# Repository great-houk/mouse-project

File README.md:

# Custom Mouse V1.0

This project is an all contains every piece you would need to fully order, assemble, and program a completely open source mouse.

This is only the first version of this mouse, and the end goal of this project is no where near complete. However, this first version does 100% work 90% of the time, so the inital goal of making a mouse is complete. In fact, I'm using it to write this readme. Pretty neat.

My immediate goal is to implement the wireless protocol over the SR1020 radio.

Future versions of this project won't use a barebones $15 dollar mouse off of amazon, and will have much higher quality everything, while also hopefully being cheaper. I used a lot of parts on this, like the MAX32625, because they looked cool. The 32625 has a one of a kind PMU, which is something like another set of super low power cores you can manually program through assembly. While this seems awesome at first, and like the perfect tool to reach extra efficient power targets, in the end the sensor draws >20mW anyway, so the difference of ~1-2mW the PMU provides is useless, and so it the extra cost.

# Notes for making your own

This is the mouse I bought and used as a base: [Amazon Link](https://www.amazon.com/gp/product/B07ZHFCM43/ref=ppx_yo_dt_b_search_asin_title?ie=UTF8&th=1)

For obtaining the other parts:
1. Most mouse parts can be desoldered from the mouse itself. I only bought one switch for the dongle off of digikey.
2. All other digital parts except the sensor can be obtained from digikey for reasonable prices, and the objects in the Kicad PCB should have digikey links associated with them already.
3. The mouse sensor is hard to get. If you are a student like me, you might be able to get a free sample from Pixart. If you aren't there are a couple of ebay postings or other second hand sellers which might offer them, but they take a while (>month normally) to ship. Pixart does offer to sell the sensors directly, but there is a minimum order quantity of 25.
4. I used JLCPCB to obtain the PCB. I had them make a stencil as well, in order to greatly simply to soldering process. For anyone in the US, chances are JLC is your best bet, for Europe, I've heard of other cheap PCB manufacturers which might do a better job, as long as the shipping isn't prohibitively expensive.
5. Programming the MCU. I used the [MCU Link](https://www.nxp.com/design/microcontrollers-developer-resources/mcu-link-debug-probe:MCU-LINK) with OpenOCD to program the chip, which had all the features I ended up needing. Maxim offers a custom fork of OpenOCD which comes the neccessary files for uploading to the MAX32625, and I made a simple custom file for the MCU Link, which is inside of the mouse folder. You need to place that file in the OpenOCD board config directory, and most online tutuorials should cover that.

The PCB is specifically designed around fitting in the mouse, and even then there were some mistakes I made. Most notably, the top right post hole was misplaced, so that needs to be cut flush so the PCB can rest flat. The antenna also sticks out the side, so you need to cut some small segments off of the casing in order to have it fit. Finally, the USB-C port is in a slightly lower and different place, so you need to cut the sides of the USB port out to have it fit and be accessible.

It took me many tries to assemble this properly, partially because it was my first time using solder past (which by the way is 100% what you need to use to solder this), and partially because there are no good resources out there for solder of this kind, at least that I could find. If you order the PCB from JLCPCB like I did, make sure to get a stencil, as it will make everything signifigantly easier. There is no need to order a stencil for the back, however, that only requires some careful soldering.

The most important parts when assembling the board are
1. Make sure you spread the paste over the stencil the fewest possible times, preferably in one strong, slow swipe. A good solder paste application makes this process signifigantly easier.
2. Don't leave the paste sitting for too long. You can take your time placing the parts, but after around 2-3 hours the paste will start drying and harden, making parts have a signifigantly higher risk of being blown away when using the heat gun.
3. Make sure to not have the temps too high. I broke my first few boards by creating shorts through burned flux. Don't do what I did.

And that's mostly it. There are other resources out there to help with the specifics, but that covers most of the general details.

# Project Structure

Each folder has it's own README which describes what it does, how it works, and how to use it, except the PCB.

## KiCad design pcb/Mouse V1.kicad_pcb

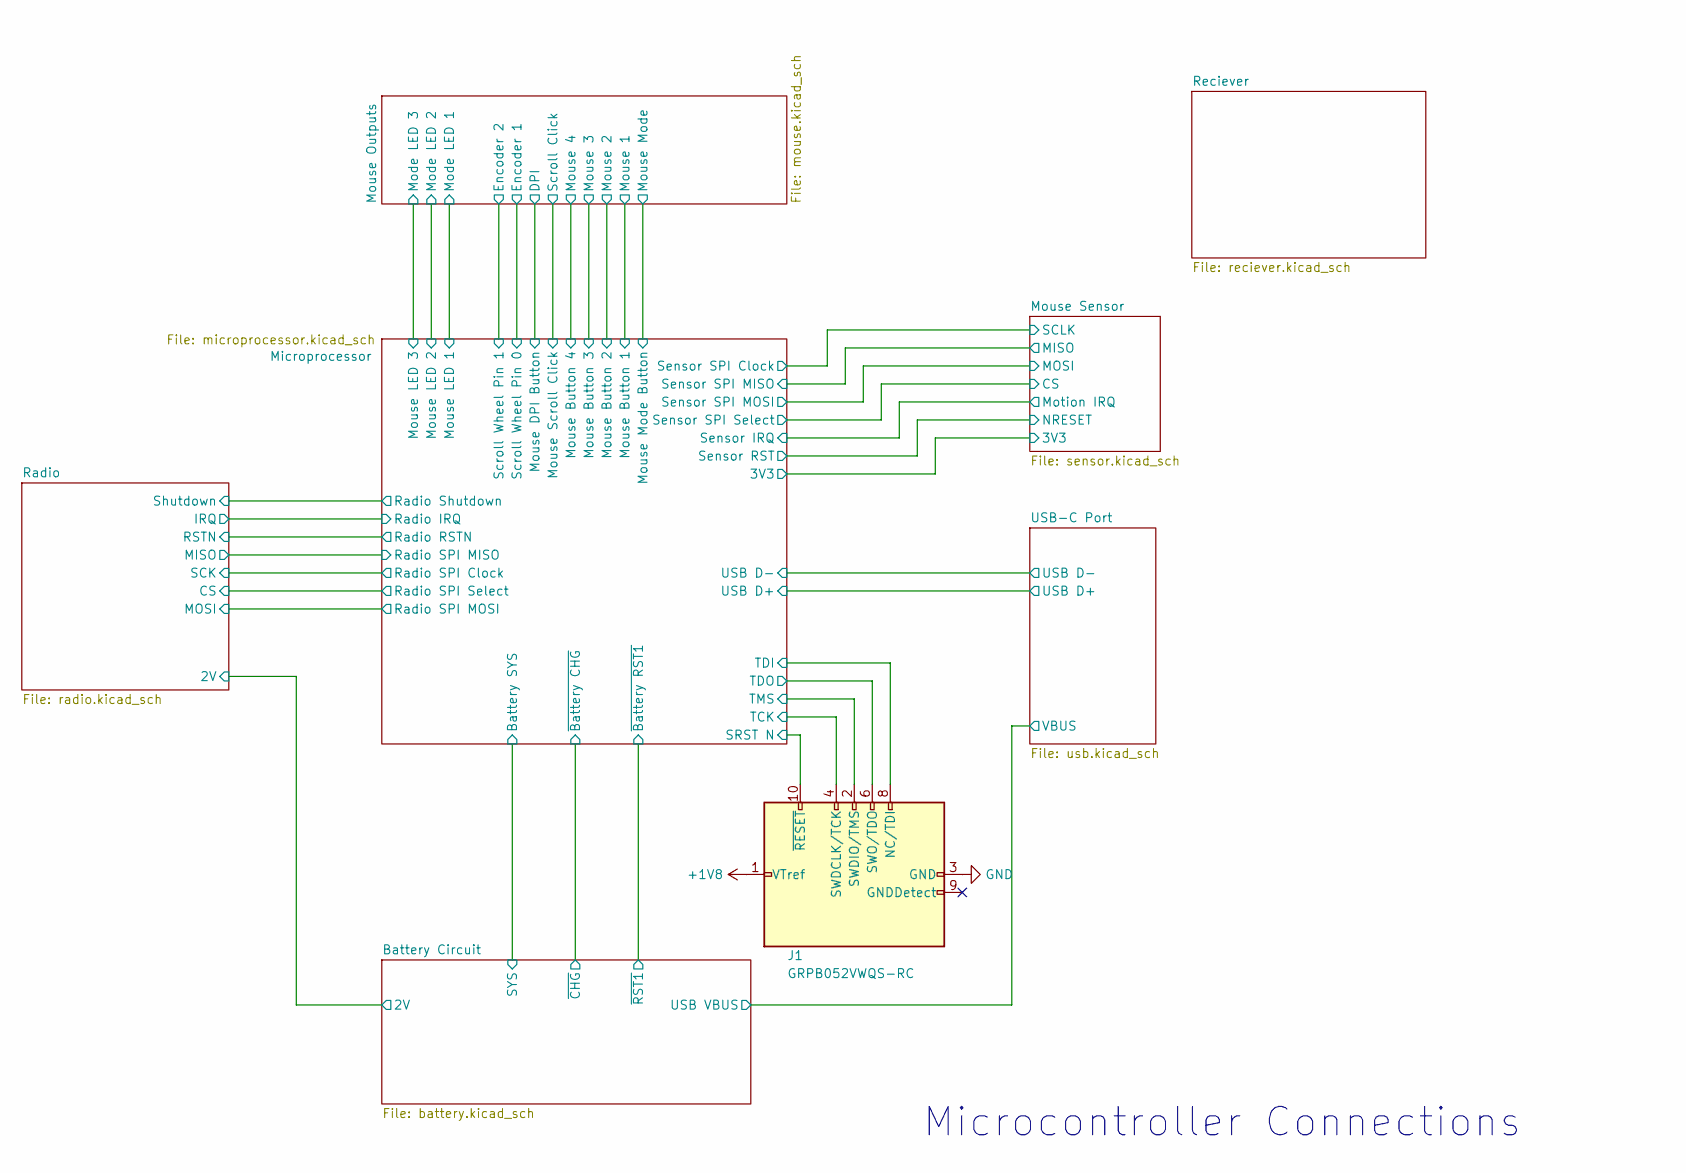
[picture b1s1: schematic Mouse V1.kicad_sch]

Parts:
J1: GRPB052VWQS-RC; PinHeader_2x05_P1.27mm_Vertical_SMD; DIGIKEY GRPB052VWQS-RC

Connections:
+1V8: J1.1 (VTref); also elsewhere on the board
/Microprocessor/SRST N: J1.10 (~RESET); also elsewhere on the board
/Microprocessor/TCK: J1.4 (SWDCLK/TCK); also elsewhere on the board
/Microprocessor/TDI: J1.8 (NC/TDI); also elsewhere on the board
/Microprocessor/TDO: J1.6 (SWO/TDO); also elsewhere on the board
/Microprocessor/TMS: J1.2 (SWDIO/TMS); also elsewhere on the board
GND: J1.3 (GND), J1.5 (GND); also elsewhere on the board

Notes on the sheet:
Microcontroller Connections

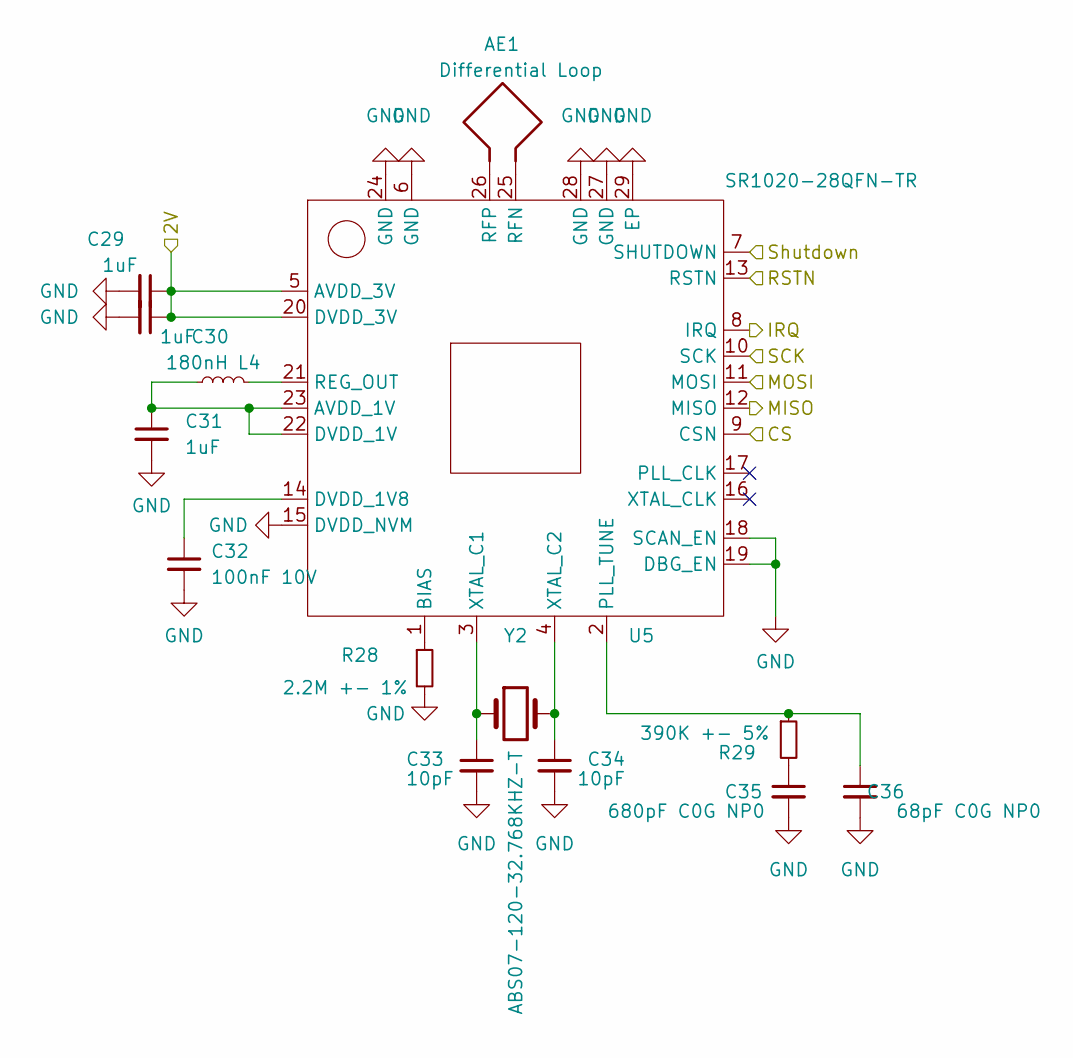
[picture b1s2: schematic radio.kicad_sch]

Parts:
AE1: Differential Loop; SR1020 Antenna Vivaldi
C29, C30, C31: 1uF; C_0603_1608Metric; DIGIKEY CL10A105KA8NNNC
C32: 100nF 10V; C_0603_1608Metric; DIGIKEY CL10B104KB8NNWC
C33, C34: 10pF; C_0603_1608Metric; DIGIKEY 06035A100JAT2A
C35: 680pF C0G NP0; C_0603_1608Metric; DIGIKEY 0603N681J500CT
C36: 68pF C0G NP0; C_0603_1608Metric; DIGIKEY CL10C680JB8NNNC
L4: 180nH; L_0603_1608Metric; DIGIKEY MLJ1608WR18JT000
R28: 2.2M +- 1%; R_0603_1608Metric; DIGIKEY RC0603FR-072M2L
R29: 390K +- 5%; R_0603_1608Metric; DIGIKEY RMCF0603JT390K
U5: SR1020-28QFN-TR; QFN-28-1EP_4x4mm_P0.4mm_EP2.6x2.6mm; DIGIKEY SR1020-28QFN-TR
Y2: ABS07-120-32.768KHZ-T; Crystal_SMD_3215-2Pin_3.2x1.5mm; DIGIKEY ABS07-120-32.768KHZ-T

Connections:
/Battery Circuit/2V: C29.1, C30.1, U5.5 (AVDD_3V), U5.20 (DVDD_3V); also elsewhere on the board
/Microprocessor/Radio IRQ: U5.8 (IRQ); also elsewhere on the board
/Microprocessor/Radio RSTN: U5.13 (RSTN); also elsewhere on the board
/Microprocessor/Radio SPI Clock: U5.10 (SCK); also elsewhere on the board
/Microprocessor/Radio SPI MISO: U5.12 (MISO); also elsewhere on the board
/Microprocessor/Radio SPI MOSI: U5.11 (MOSI); also elsewhere on the board
/Microprocessor/Radio SPI Select: U5.9 (CSN); also elsewhere on the board
/Microprocessor/Radio Shutdown: U5.7 (SHUTDOWN); also elsewhere on the board
GND: C29.2, C30.2, C31.2, C32.2, C33.2, C34.2, C35.2, C36.2, R28.2, U5.6 (GND), U5.15 (DVDD_NVM), U5.18 (SCAN_EN), U5.19 (DBG_EN), U5.24 (GND), U5.27 (GND), U5.28 (GND), U5.29 (EP); also elsewhere on the board
unnamed: AE1.1, U5.26 (RFP)
unnamed: AE1.2, U5.25 (RFN)
unnamed: C31.1, L4.1, U5.22 (DVDD_1V), U5.23 (AVDD_1V)
unnamed: C32.1, U5.14 (DVDD_1V8)
unnamed: C33.1, U5.3 (XTAL_C1), Y2.1
unnamed: C34.1, U5.4 (XTAL_C2), Y2.2
unnamed: C35.1, R29.2
unnamed: C36.1, R29.1, U5.2 (PLL_TUNE)
unnamed: L4.2, U5.21 (REG_OUT)
unnamed: R28.1, U5.1 (BIAS)

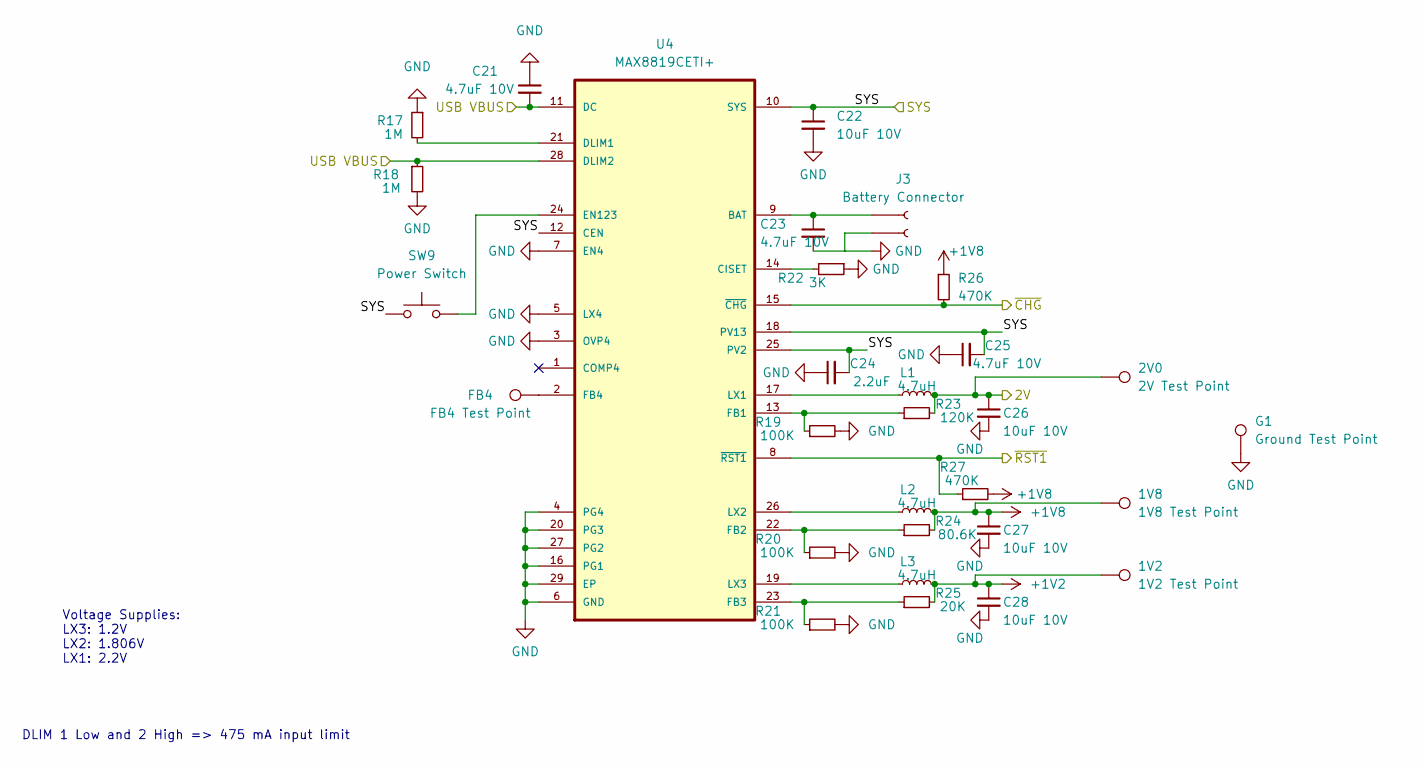
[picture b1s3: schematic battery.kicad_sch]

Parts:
1V2: 1V2 Test Point; TestPoint_Pad_D1.0mm
1V8: 1V8 Test Point; TestPoint_Pad_D1.0mm
2V0: 2V Test Point; TestPoint_Pad_D1.0mm
C21, C23, C25: 4.7uF 10V; C_0603_1608Metric; DIGIKEY CL10A475KP8NNNC
C22, C26, C27, C28: 10uF 10V; C_0603_1608Metric; DIGIKEY 0603ZD106KAT2A
C24: 2.2uF; C_0603_1608Metric; DIGIKEY CL10A225KP8NNNC
FB4: FB4 Test Point; TestPoint_Pad_D2.0mm
G1: Ground Test Point; TestPoint_Pad_D1.0mm
J3: Battery Connector; JST_PH_B2B-PH-K_1x02_P2.00mm_Vertical
L1, L2, L3: 4.7uH; L_Taiyo-Yuden_MD-2020; DIGIKEY VLS201612CX-4R7M-1
R17, R18: 1M; R_0603_1608Metric; DIGIKEY RMCF0603FT1M00
R19, R20, R21: 100K; R_0603_1608Metric; DIGIKEY RMCF0603FT100K
R22: 3K; R_0603_1608Metric; DIGIKEY RMCF0603JT3K00
R23: 120K; R_0603_1608Metric; DIGIKEY RMCF0603FT120K
R24: 80.6K; R_0603_1608Metric; DIGIKEY RMCF0603FT80K6
R25: 20K; R_0603_1608Metric; DIGIKEY RMCF0603FT20K0
R26, R27: 470K; R_0603_1608Metric; DIGIKEY RMCF0603JT470K
SW9: Power Switch; SW_SPDT_PCM12; DIGIKEY Have
U4: MAX8819CETI+; QFN40P400X400X80-29N; DIGIKEY MAX8819CETI+

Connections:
+1V2: 1V2.1, C28.1, L3.2, R25.2; also elsewhere on the board
+1V8: 1V8.1, C27.1, L2.2, R24.2, R26.1, R27.2; also elsewhere on the board
/Battery Circuit/2V: 2V0.1, C26.1, L1.2, R23.2; also elsewhere on the board
/Battery Circuit/SYS: C22.1, C24.2, C25.2, SW9.1, U4.10 (SYS), U4.12 (CEN), U4.18 (PV13), U4.25 (PV2); also elsewhere on the board
/Battery Circuit/USB VBUS: C21.2, R18.1, U4.11 (DC), U4.28 (DLIM2); also elsewhere on the board
/Battery Circuit/~CHG: R26.2, U4.15 (~CHG); also elsewhere on the board
/Battery Circuit/~RST1: R27.1, U4.8 (~RST1); also elsewhere on the board
GND: C21.1, C22.2, C23.2, C24.1, C25.1, C26.2, C27.2, C28.2, G1.1, J3.1, R17.1, R18.2, R19.2, R20.2, R21.2, R22.1, U4.3 (OVP4), U4.4 (PG4), U4.5 (LX4), U4.6 (GND), U4.7 (EN4), U4.16 (PG1), U4.20 (PG3), U4.27 (PG2), U4.29 (EP); also elsewhere on the board
unnamed: C23.1, J3.2, U4.9 (BAT)
unnamed: FB4.1, U4.2 (FB4)
unnamed: L1.1, U4.17 (LX1)
unnamed: L2.1, U4.26 (LX2)
unnamed: L3.1, U4.19 (LX3)
unnamed: R17.2, U4.21 (DLIM1)
unnamed: R19.1, R23.1, U4.13 (FB1)
unnamed: R20.1, R24.1, U4.22 (FB2)
unnamed: R21.1, R25.1, U4.23 (FB3)
unnamed: R22.2, U4.14 (CISET)
unnamed: SW9.2, U4.24 (EN123)

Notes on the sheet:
DLIM 1 Low and 2 High => 475 mA input limit
Voltage Supplies: LX3: 1.2V LX2: 1.806V LX1: 2.2V

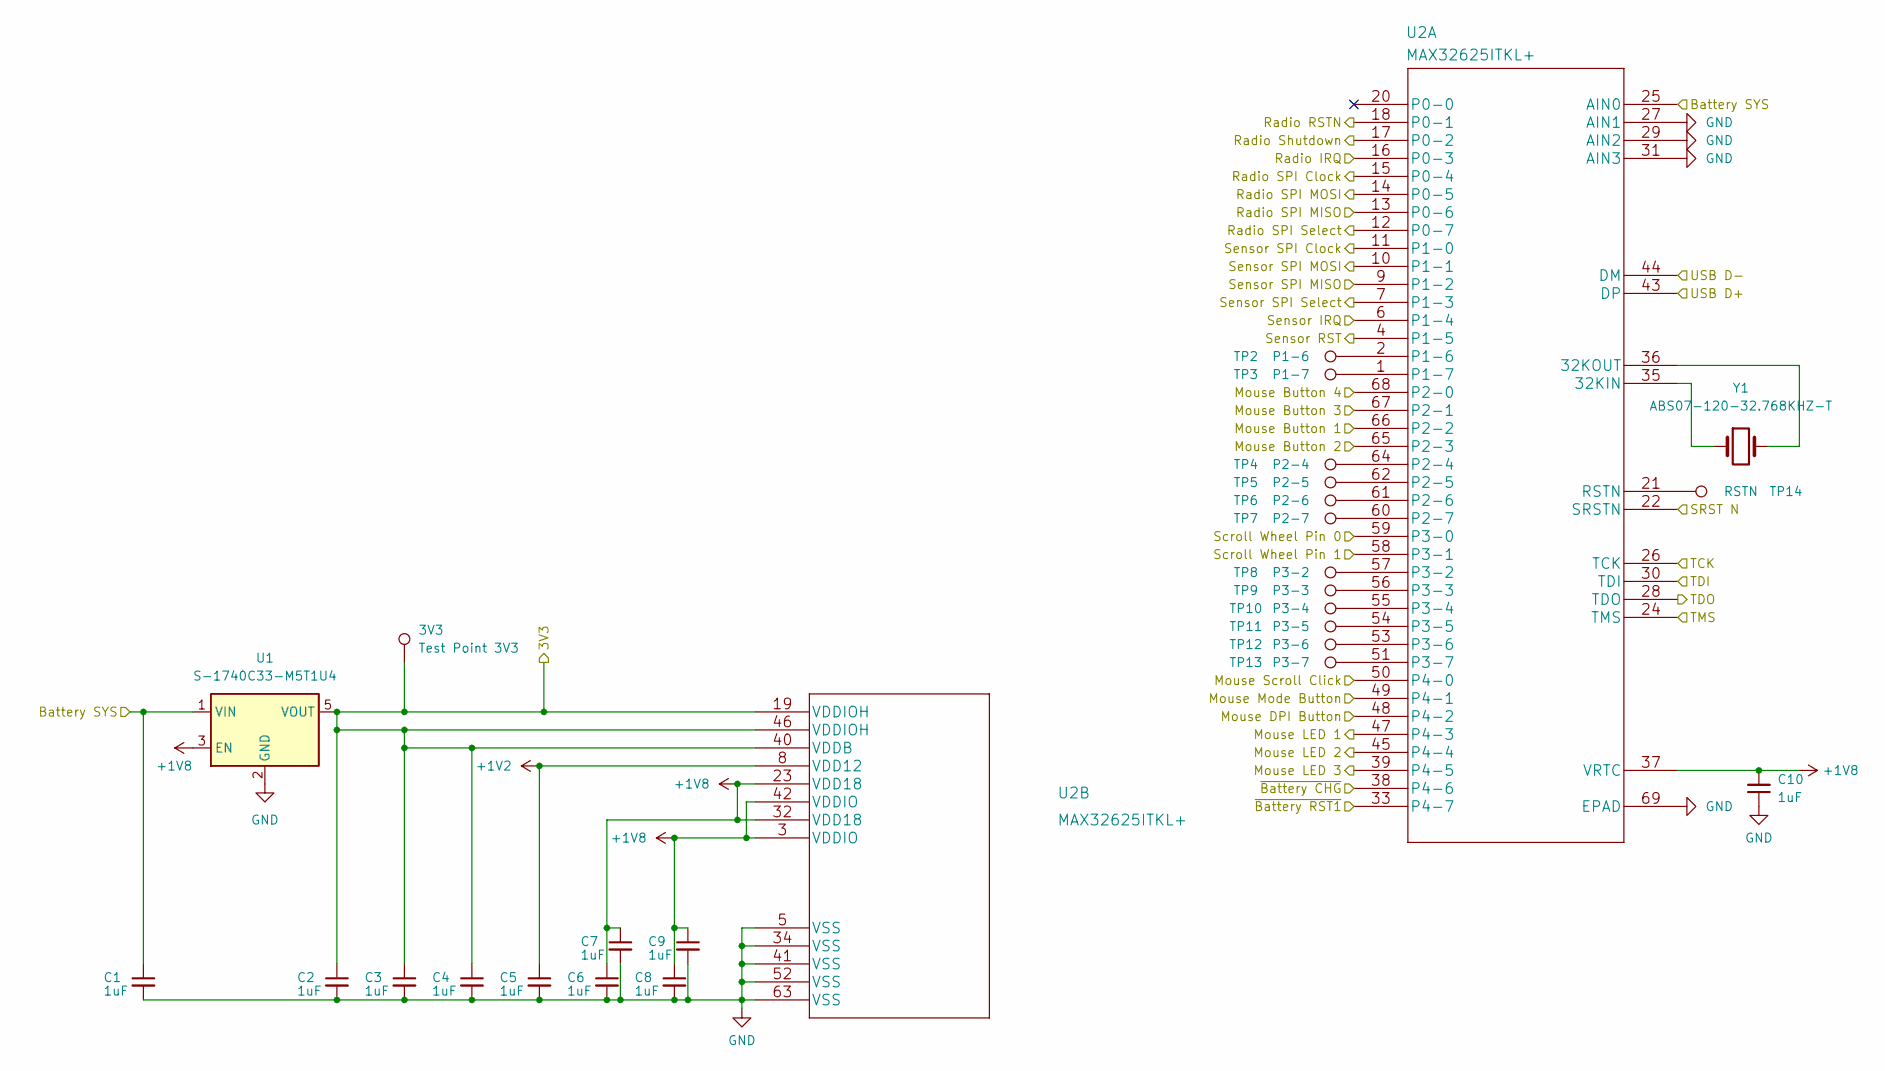
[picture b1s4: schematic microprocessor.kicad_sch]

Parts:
3V3: Test Point 3V3; TestPoint_Pad_D1.0mm
C1, C2, C3, C4, C5, C6, C7, C8, C9, C10: 1uF; C_0603_1608Metric; DIGIKEY CL10A105KA8NNNC
TP2: P1-6; TestPoint_Pad_D1.0mm
TP3: P1-7; TestPoint_Pad_D1.0mm
TP4: P2-4; TestPoint_Pad_D1.0mm
TP5: P2-5; TestPoint_Pad_D1.0mm
TP6: P2-6; TestPoint_Pad_D1.0mm
TP7: P2-7; TestPoint_Pad_D1.0mm
TP8: P3-2; TestPoint_Pad_D1.0mm
TP9: P3-3; TestPoint_Pad_D1.0mm
TP10: P3-4; TestPoint_Pad_D1.0mm
TP11: P3-5; TestPoint_Pad_D1.0mm
TP12: P3-6; TestPoint_Pad_D1.0mm
TP13: P3-7; TestPoint_Pad_D1.0mm
TP14: RSTN; TestPoint_Pad_D1.0mm
U1: S-1740C33-M5T1U4; TSOT-23-5; DIGIKEY S-1740C33-M5T1U4
U2: MAX32625ITKL+; MAX32625ITKL&plus_; DIGIKEY MAX32625ITKL+
Y1: ABS07-120-32.768KHZ-T; Crystal_SMD_3215-2Pin_3.2x1.5mm; DIGIKEY ABS07-120-32.768KHZ-T

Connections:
+1V2: C5.1, U2.8 (VDD12); also elsewhere on the board
+1V8: C6.1, C7.1, C8.1, C9.1, C10.2, U1.3 (EN), U2.3 (VDDIO), U2.23 (VDD18), U2.32 (VDD18), U2.37 (VRTC), U2.42 (VDDIO); also elsewhere on the board
/Battery Circuit/SYS: C1.1, U1.1 (VIN), U2.25 (AIN0); also elsewhere on the board
/Battery Circuit/~CHG: U2.38 (P4-6); also elsewhere on the board
/Battery Circuit/~RST1: U2.33 (P4-7); also elsewhere on the board
/Microprocessor/3V3: 3V3.1, C2.1, C3.1, C4.1, U1.5 (VOUT), U2.19 (VDDIOH), U2.40 (VDDB), U2.46 (VDDIOH); also elsewhere on the board
/Microprocessor/Mouse Button 1: U2.66 (P2-2); also elsewhere on the board
/Microprocessor/Mouse Button 2: U2.65 (P2-3); also elsewhere on the board
/Microprocessor/Mouse Button 3: U2.67 (P2-1); also elsewhere on the board
/Microprocessor/Mouse Button 4: U2.68 (P2-0); also elsewhere on the board
/Microprocessor/Mouse DPI Button: U2.48 (P4-2); also elsewhere on the board
/Microprocessor/Mouse LED 1: U2.47 (P4-3); also elsewhere on the board
/Microprocessor/Mouse LED 2: U2.45 (P4-4); also elsewhere on the board
/Microprocessor/Mouse LED 3: U2.39 (P4-5); also elsewhere on the board
/Microprocessor/Mouse Mode Button: U2.49 (P4-1); also elsewhere on the board
/Microprocessor/Mouse Scroll Click: U2.50 (P4-0); also elsewhere on the board
/Microprocessor/Radio IRQ: U2.16 (P0-3); also elsewhere on the board
/Microprocessor/Radio RSTN: U2.18 (P0-1); also elsewhere on the board
/Microprocessor/Radio SPI Clock: U2.15 (P0-4); also elsewhere on the board
/Microprocessor/Radio SPI MISO: U2.13 (P0-6); also elsewhere on the board
/Microprocessor/Radio SPI MOSI: U2.14 (P0-5); also elsewhere on the board
/Microprocessor/Radio SPI Select: U2.12 (P0-7); also elsewhere on the board
/Microprocessor/Radio Shutdown: U2.17 (P0-2); also elsewhere on the board
/Microprocessor/SRST N: U2.22 (SRSTN); also elsewhere on the board
/Microprocessor/Scroll Wheel Pin 0: U2.59 (P3-0); also elsewhere on the board
/Microprocessor/Scroll Wheel Pin 1: U2.58 (P3-1); also elsewhere on the board
/Microprocessor/Sensor IRQ: U2.6 (P1-4); also elsewhere on the board
/Microprocessor/Sensor RST: U2.4 (P1-5); also elsewhere on the board
/Microprocessor/Sensor SPI Clock: U2.11 (P1-0); also elsewhere on the board
/Microprocessor/Sensor SPI MISO: U2.9 (P1-2); also elsewhere on the board
/Microprocessor/Sensor SPI MOSI: U2.10 (P1-1); also elsewhere on the board
/Microprocessor/Sensor SPI Select: U2.7 (P1-3); also elsewhere on the board
/Microprocessor/TCK: U2.26 (TCK); also elsewhere on the board
/Microprocessor/TDI: U2.30 (TDI); also elsewhere on the board
/Microprocessor/TDO: U2.28 (TDO); also elsewhere on the board
/Microprocessor/TMS: U2.24 (TMS); also elsewhere on the board
/Microprocessor/USB D+: U2.43 (DP); also elsewhere on the board
/Microprocessor/USB D-: U2.44 (DM); also elsewhere on the board
GND: C1.2, C2.2, C3.2, C4.2, C5.2, C6.2, C7.2, C8.2, C9.2, C10.1, U1.2 (GND), U2.5 (VSS), U2.27 (AIN1), U2.29 (AIN2), U2.31 (AIN3), U2.34 (VSS), U2.41 (VSS), U2.52 (VSS), U2.63 (VSS), U2.69 (EPAD); also elsewhere on the board
unnamed: TP2.1, U2.2 (P1-6)
unnamed: TP3.1, U2.1 (P1-7)
unnamed: TP4.1, U2.64 (P2-4)
unnamed: TP5.1, U2.62 (P2-5)
unnamed: TP6.1, U2.61 (P2-6)
unnamed: TP7.1, U2.60 (P2-7)
unnamed: TP8.1, U2.57 (P3-2)
unnamed: TP9.1, U2.56 (P3-3)
unnamed: TP10.1, U2.55 (P3-4)
unnamed: TP11.1, U2.54 (P3-5)
unnamed: TP12.1, U2.53 (P3-6)
unnamed: TP13.1, U2.51 (P3-7)
unnamed: TP14.1, U2.21 (RSTN)
unnamed: U2.35 (32KIN), Y1.1
unnamed: U2.36 (32KOUT), Y1.2

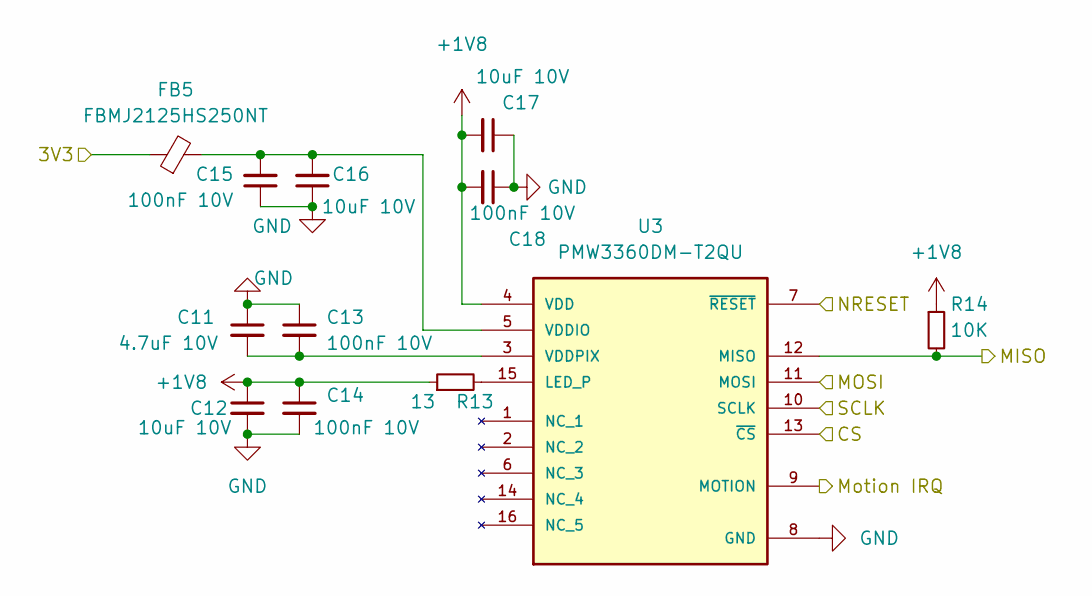
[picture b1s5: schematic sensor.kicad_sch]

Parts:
C11: 4.7uF 10V; C_0603_1608Metric; DIGIKEY CL10A475KP8NNNC
C12, C16, C17: 10uF 10V; C_0603_1608Metric; DIGIKEY 0603ZD106KAT2A
C13, C14, C15, C18: 100nF 10V; C_0603_1608Metric; DIGIKEY CL10B104KB8NNWC
FB5: FBMJ2125HS250NT; L_0805_2012Metric; DIGIKEY FBMJ2125HS250NT
R13: 13; R_0603_1608Metric; DIGIKEY RMCF0603FT13R0
R14: 10K; R_0603_1608Metric; DIGIKEY RNCP0603FTD10K0
U3: PMW3360DM-T2QU; MANUFACTURER_PART_NUMBER PMW3360DM-T2QU; DIGIKEY PMW3360DM-T2QU

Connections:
+1V8: C12.1, C14.1, C17.2, C18.2, R13.1, R14.1, U3.4 (VDD); also elsewhere on the board
/Microprocessor/3V3: FB5.1; also elsewhere on the board
/Microprocessor/Sensor IRQ: U3.9 (MOTION); also elsewhere on the board
/Microprocessor/Sensor RST: U3.7 (~RESET); also elsewhere on the board
/Microprocessor/Sensor SPI Clock: U3.10 (SCLK); also elsewhere on the board
/Microprocessor/Sensor SPI MISO: R14.2, U3.12 (MISO); also elsewhere on the board
/Microprocessor/Sensor SPI MOSI: U3.11 (MOSI); also elsewhere on the board
/Microprocessor/Sensor SPI Select: U3.13 (~CS); also elsewhere on the board
GND: C11.1, C12.2, C13.1, C14.2, C15.1, C16.1, C17.1, C18.1, U3.8 (GND); also elsewhere on the board
unnamed: C11.2, C13.2, U3.3 (VDDPIX)
unnamed: C15.2, C16.2, FB5.2, U3.5 (VDDIO)
unnamed: R13.2, U3.15 (LED_P)

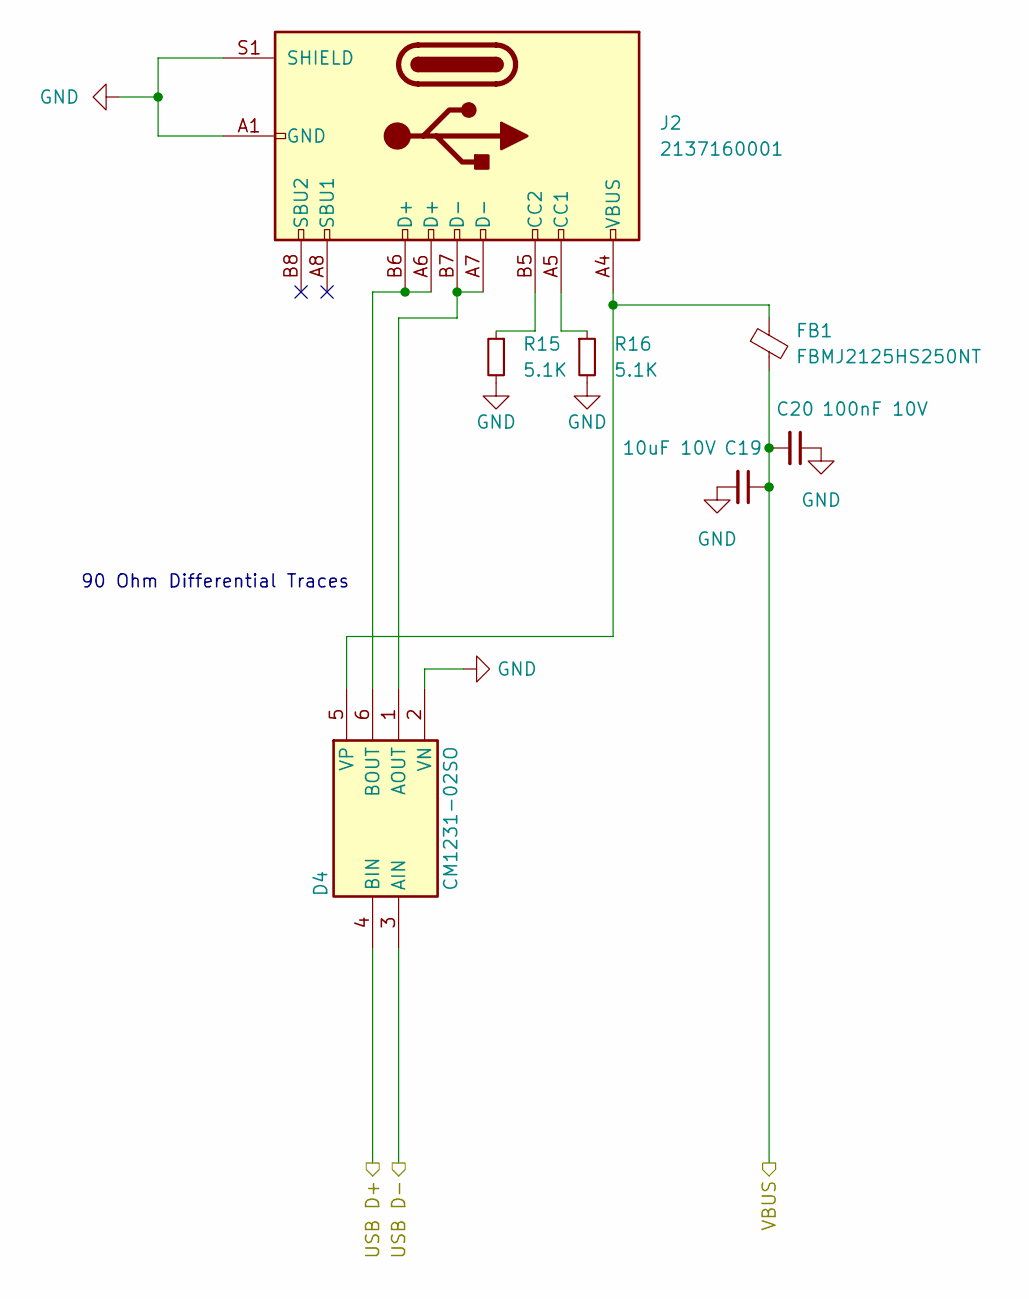
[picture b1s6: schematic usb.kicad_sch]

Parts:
C19: 10uF 10V; C_0603_1608Metric; DIGIKEY 0603ZD106KAT2A
C20: 100nF 10V; C_0603_1608Metric; DIGIKEY CL10B104KB8NNWC
D4: CM1231-02SO; Standoff Voltage 5V; Manufacturer Part Number CM1231-02SO; DIGIKEY CM1231-02SO
FB1: FBMJ2125HS250NT; L_0805_2012Metric; DIGIKEY FBMJ2125HS250NT
J2: 2137160001; USB_C_Receptacle_JAE_DX07S016JA1R1500; DIGIKEY 2137160001
R15, R16: 5.1K; R_0603_1608Metric; DIGIKEY RMCF0603JT5K10

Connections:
/Battery Circuit/USB VBUS: C19.1, C20.2, FB1.2; also elsewhere on the board
/Microprocessor/USB D+: D4.4 (BIN); also elsewhere on the board
/Microprocessor/USB D-: D4.3 (AIN); also elsewhere on the board
GND: C19.2, C20.1, D4.2 (VN), J2.A1 (GND), J2.A12 (GND), J2.B1 (GND), J2.B12 (GND), J2.S1 (SHIELD), R15.2, R16.2; also elsewhere on the board
unnamed: D4.1 (AOUT), J2.A7 (D-), J2.B7 (D-)
unnamed: D4.5 (VP), FB1.1, J2.A4 (VBUS), J2.A9 (VBUS), J2.B4 (VBUS), J2.B9 (VBUS)
unnamed: D4.6 (BOUT), J2.A6 (D+), J2.B6 (D+)
unnamed: J2.A5 (CC1), R16.1
unnamed: J2.B5 (CC2), R15.1

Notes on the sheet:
90 Ohm Differential Traces

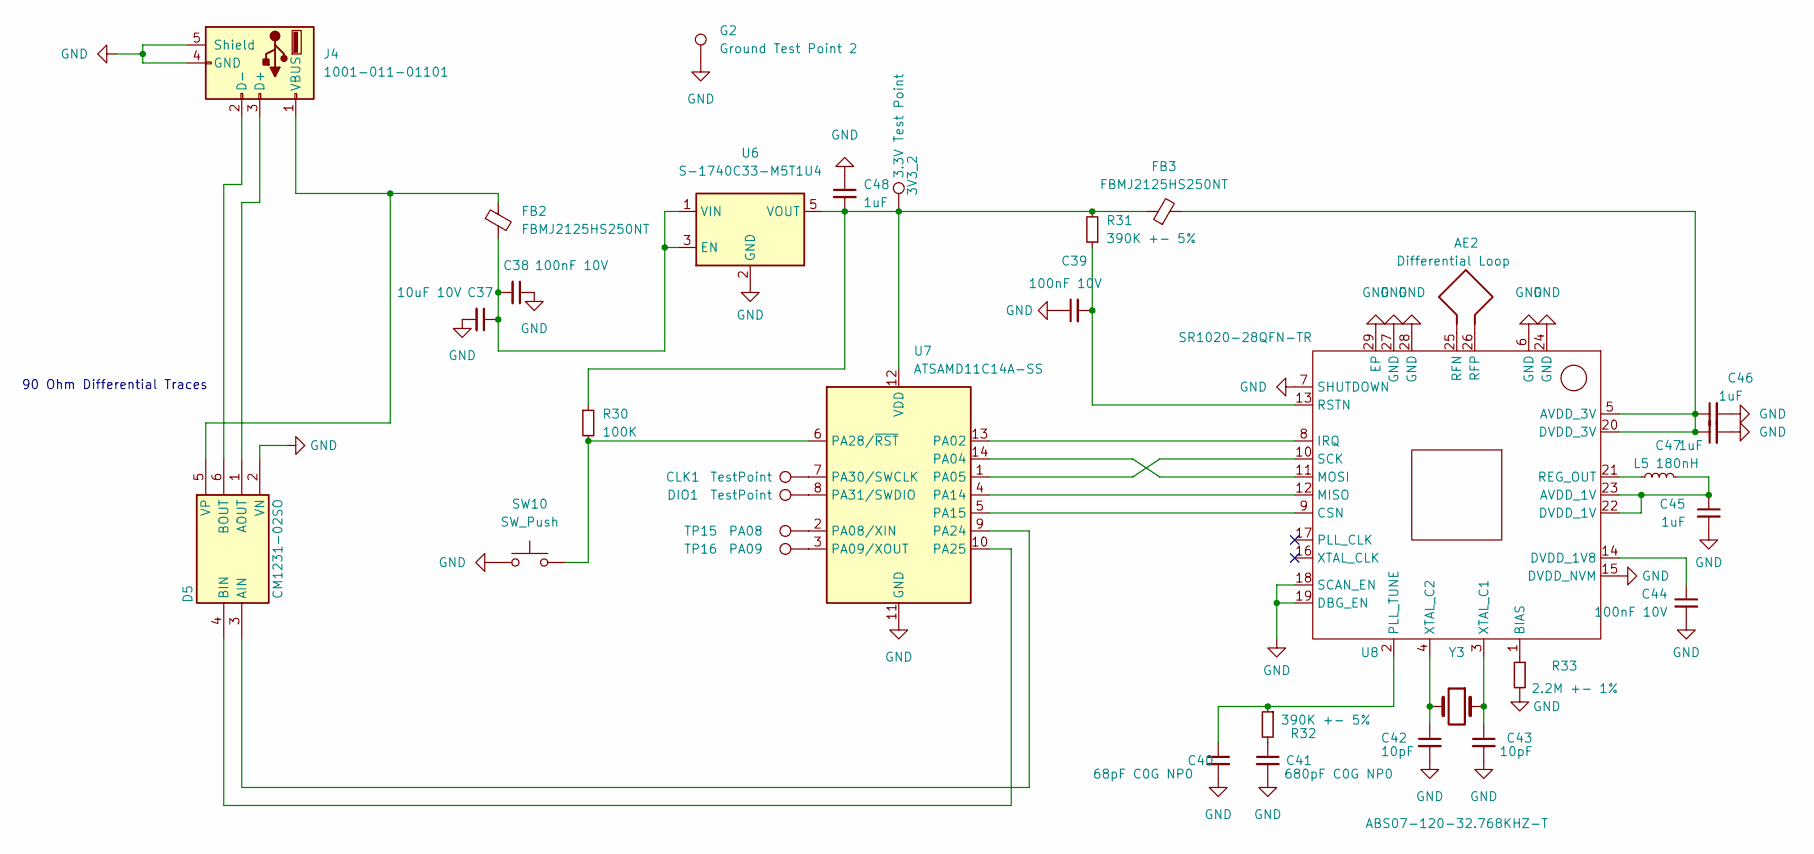
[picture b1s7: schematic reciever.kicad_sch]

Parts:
3V3_2: 3.3V Test Point; TestPoint_Pad_D1.0mm
AE2: Differential Loop; SR1020 Antenna Vivaldi
C37: 10uF 10V; C_0603_1608Metric; DIGIKEY 0603ZD106KAT2A
C38, C39, C44: 100nF 10V; C_0603_1608Metric; DIGIKEY CL10B104KB8NNWC
C40: 68pF C0G NP0; C_0603_1608Metric; DIGIKEY CL10C680JB8NNNC
C41: 680pF C0G NP0; C_0603_1608Metric; DIGIKEY 0603N681J500CT
C42, C43: 10pF; C_0603_1608Metric; DIGIKEY 06035A100JAT2A
C45, C46, C47, C48: 1uF; C_0603_1608Metric; DIGIKEY CL10A105KA8NNNC
CLK1: TestPoint; TestPoint_Pad_D1.0mm
D5: CM1231-02SO; Standoff Voltage 5V; Manufacturer Part Number CM1231-02SO; DIGIKEY CM1231-02SO
DIO1: TestPoint; TestPoint_Pad_D1.0mm
FB2, FB3: FBMJ2125HS250NT; L_0805_2012Metric; DIGIKEY FBMJ2125HS250NT
G2: Ground Test Point 2; TestPoint_Pad_D1.0mm
J4: 1001-011-01101; USB_A_CNCTech_1001-011-01101_Horizontal; DIGIKEY 1001-011-01101
L5: 180nH; L_0603_1608Metric; DIGIKEY MLJ1608WR18JT000
R30: 100K; R_0603_1608Metric; DIGIKEY RMCF0603FT100K
R31, R32: 390K +- 5%; R_0603_1608Metric; DIGIKEY RMCF0603JT390K
R33: 2.2M +- 1%; R_0603_1608Metric; DIGIKEY RC0603FR-072M2L
SW10: SW_Push; SW_SPST_B3U-1000P-B; DIGIKEY B3U-1000P-B
TP15: PA08; TestPoint_Pad_D1.0mm
TP16: PA09; TestPoint_Pad_D1.0mm
U6: S-1740C33-M5T1U4; TSOT-23-5; DIGIKEY S-1740C33-M5T1U4
U7: ATSAMD11C14A-SS; SOIC-14_3.9x8.7mm_P1.27mm; DIGIKEY ATSAMD11C14A-SS
U8: SR1020-28QFN-TR; QFN-28-1EP_4x4mm_P0.4mm_EP2.6x2.6mm; DIGIKEY SR1020-28QFN-TR
Y3: ABS07-120-32.768KHZ-T; Crystal_SMD_3215-2Pin_3.2x1.5mm; DIGIKEY ABS07-120-32.768KHZ-T

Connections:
GND: C37.2, C38.1, C39.1, C40.2, C41.2, C42.2, C43.2, C44.2, C45.2, C46.2, C47.2, C48.1, D5.2 (VN), G2.1, J4.4 (GND), J4.5 (Shield), R33.2, SW10.1, U6.2 (GND), U7.11 (GND), U8.6 (GND), U8.7 (SHUTDOWN), U8.15 (DVDD_NVM), U8.18 (SCAN_EN), U8.19 (DBG_EN), U8.24 (GND), U8.27 (GND), U8.28 (GND), U8.29 (EP); also elsewhere on the board
unnamed 41: 3V3_2.1, C48.2, FB3.1, R30.1, R31.2, U6.5 (VOUT), U7.12 (VDD); also elsewhere on the board
unnamed: AE2.1, U8.26 (RFP)
unnamed: AE2.2, U8.25 (RFN)
unnamed: C37.1, C38.2, FB2.2, U6.1 (VIN), U6.3 (EN)
unnamed: C39.2, R31.1, U8.13 (RSTN)
unnamed: C40.1, R32.1, U8.2 (PLL_TUNE)
unnamed: C41.1, R32.2
unnamed: C42.1, U8.4 (XTAL_C2), Y3.2
unnamed: C43.1, U8.3 (XTAL_C1), Y3.1
unnamed: C44.1, U8.14 (DVDD_1V8)
unnamed: C45.1, L5.1, U8.22 (DVDD_1V), U8.23 (AVDD_1V)
unnamed: C46.1, C47.1, FB3.2, U8.5 (AVDD_3V), U8.20 (DVDD_3V)
unnamed 64: CLK1.1, U7.7 (PA30/SWCLK); also elsewhere on the board
unnamed: D5.1 (AOUT), J4.3 (D+)
unnamed: D5.3 (AIN), U7.9 (PA24)
unnamed: D5.4 (BIN), U7.10 (PA25)
unnamed: D5.5 (VP), FB2.1, J4.1 (VBUS)
unnamed: D5.6 (BOUT), J4.2 (D-)
unnamed 76: DIO1.1, U7.8 (PA31/SWDIO); also elsewhere on the board
unnamed: L5.2, U8.21 (REG_OUT)
unnamed: R30.2, SW10.2, U7.6 (PA28/~RST)
unnamed: R33.1, U8.1 (BIAS)
unnamed: TP15.1, U7.2 (PA08/XIN)
unnamed: TP16.1, U7.3 (PA09/XOUT)
unnamed: U7.1 (PA05), U8.10 (SCK)
unnamed: U7.4 (PA14), U8.12 (MISO)
unnamed: U7.5 (PA15), U8.9 (CSN)
unnamed: U7.13 (PA02), U8.8 (IRQ)
unnamed: U7.14 (PA04), U8.11 (MOSI)

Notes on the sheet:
90 Ohm Differential Traces

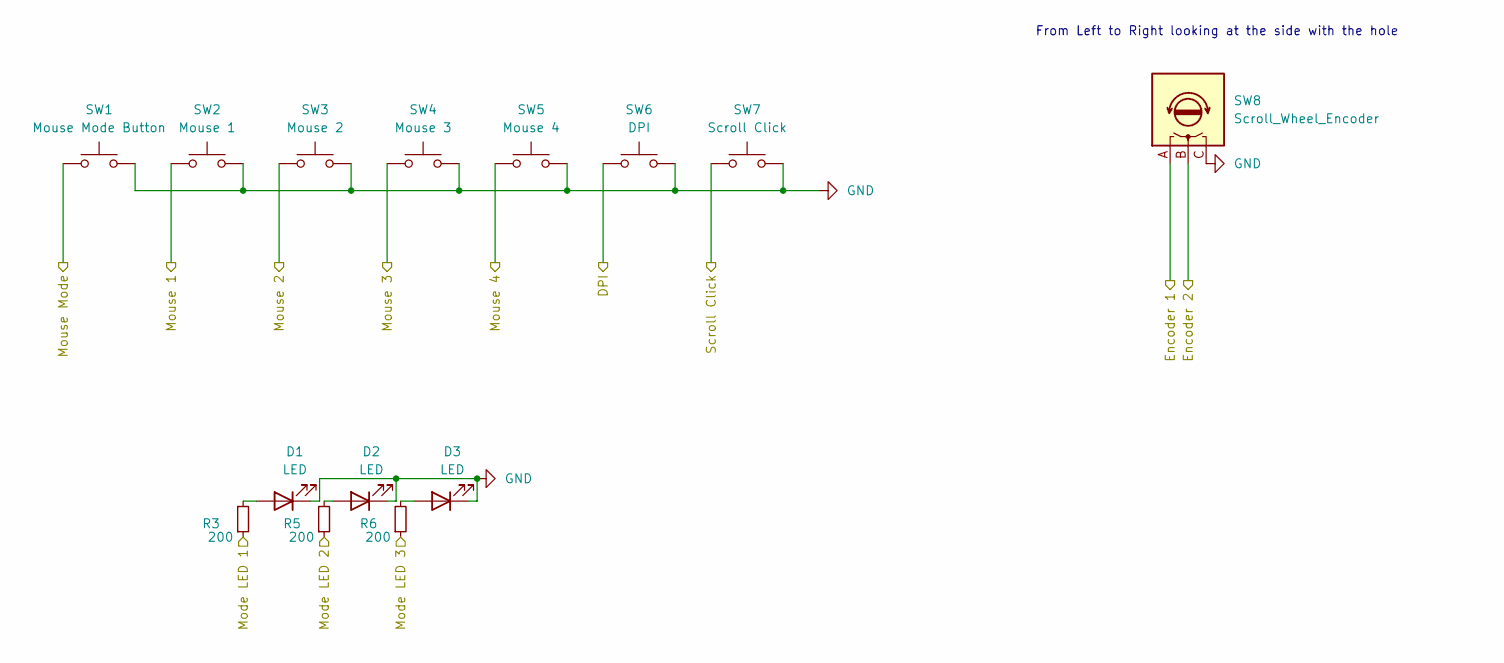
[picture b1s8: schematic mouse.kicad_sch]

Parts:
D1: LED; LED_0603_1608Metric; DIGIKEY LTST-C191KFKT
D2: LED; LED_0603_1608Metric; DIGIKEY LTST-C191KRKT
D3: LED; LED_0603_1608Metric; DIGIKEY LTST-C191KGKT
R3, R5, R6: 200; R_0603_1608Metric; DIGIKEY RNCP0603FTD200R
SW1: Mouse Mode Button; SW_PUSH_6mm; DIGIKEY Have
SW2: Mouse 1; TL59AF100Q; DIGIKEY Have
SW3: Mouse 2; TL59AF100Q; DIGIKEY Have
SW4: Mouse 3; TL59AF100Q; DIGIKEY Have
SW5: Mouse 4; TL59AF100Q; DIGIKEY Have
SW6: DPI; TL59AF100Q; DIGIKEY Have
SW7: Scroll Click; D2F-01L; DIGIKEY Have
SW8: Scroll_Wheel_Encoder; Encoder; DIGIKEY Have

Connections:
/Microprocessor/Mouse Button 2: SW3.1; also elsewhere on the board
/Microprocessor/Mouse Button 3: SW4.1; also elsewhere on the board
/Microprocessor/Mouse Button 4: SW5.1; also elsewhere on the board
/Microprocessor/Mouse DPI Button: SW6.1; also elsewhere on the board
/Microprocessor/Mouse LED 1: R3.1; also elsewhere on the board
/Microprocessor/Mouse LED 2: R5.1; also elsewhere on the board
/Microprocessor/Mouse LED 3: R6.1; also elsewhere on the board
/Microprocessor/Mouse Mode Button: SW1.1; also elsewhere on the board
/Microprocessor/Scroll Wheel Pin 0: SW8.A; also elsewhere on the board
/Microprocessor/Scroll Wheel Pin 1: SW8.B; also elsewhere on the board
GND: D1.1 (K), D2.1 (K), D3.1 (K), SW1.2, SW2.2, SW3.2, SW4.2, SW5.2, SW6.2, SW7.2, SW8.C (COM); also elsewhere on the board
unnamed: D1.2 (A), R3.2
unnamed: D2.2 (A), R5.2
unnamed: D3.2 (A), R6.2

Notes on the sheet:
From Left to Right looking at the side with the hole

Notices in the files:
parts and their libraries:
Copyright 2021 Accelerated Designs. All rights reserved.
